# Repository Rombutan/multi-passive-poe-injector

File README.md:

# multi-passive-poe-injector

Has 4 polyfused in line passive poe injectors and 4 polyfused power outputs
All outputs selectable with jumper between off, straight input, and boost converter
All the outputs also have a fully analog status LED which indicated red for fuse blown, green for good, and blue for powered off via the jumper.
Uses wiedmullers and wagos for all wire connections

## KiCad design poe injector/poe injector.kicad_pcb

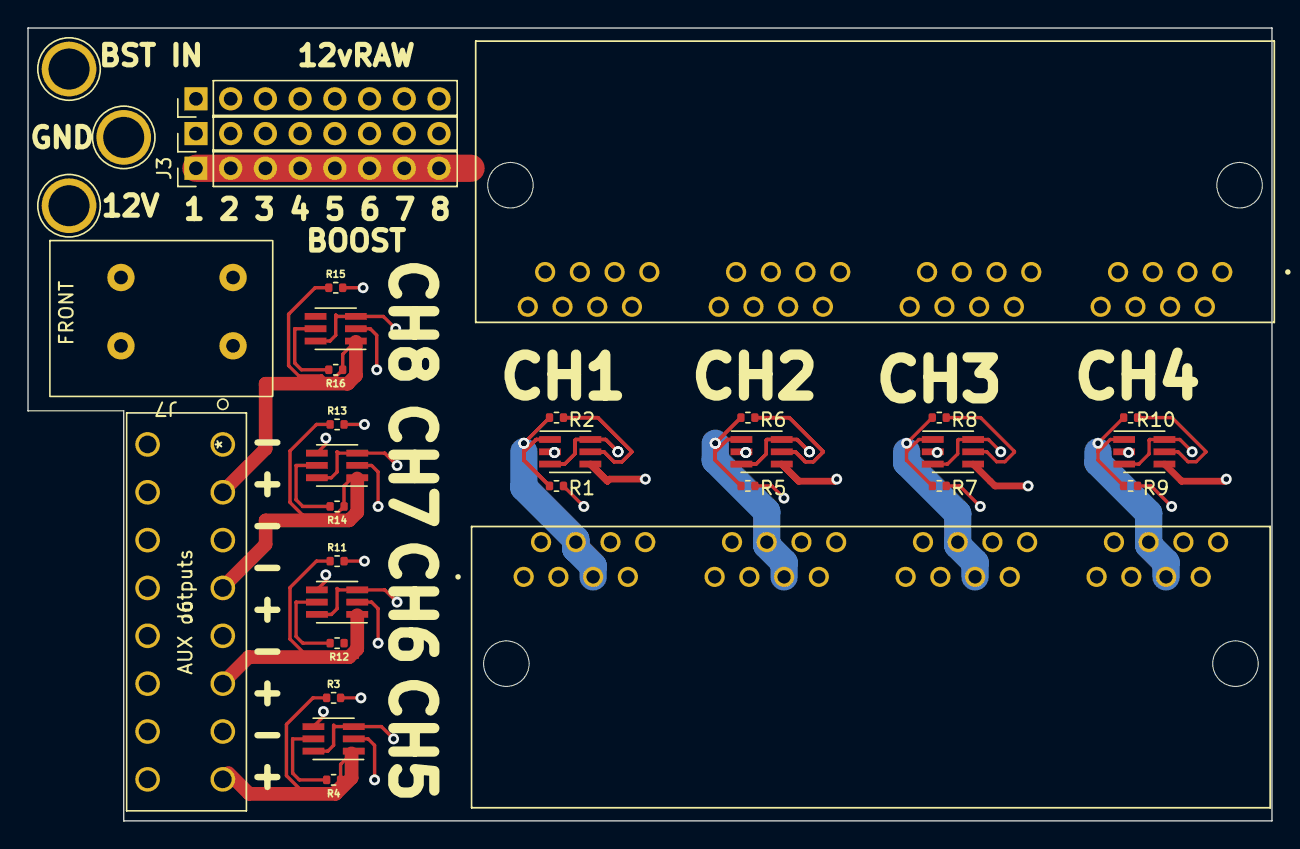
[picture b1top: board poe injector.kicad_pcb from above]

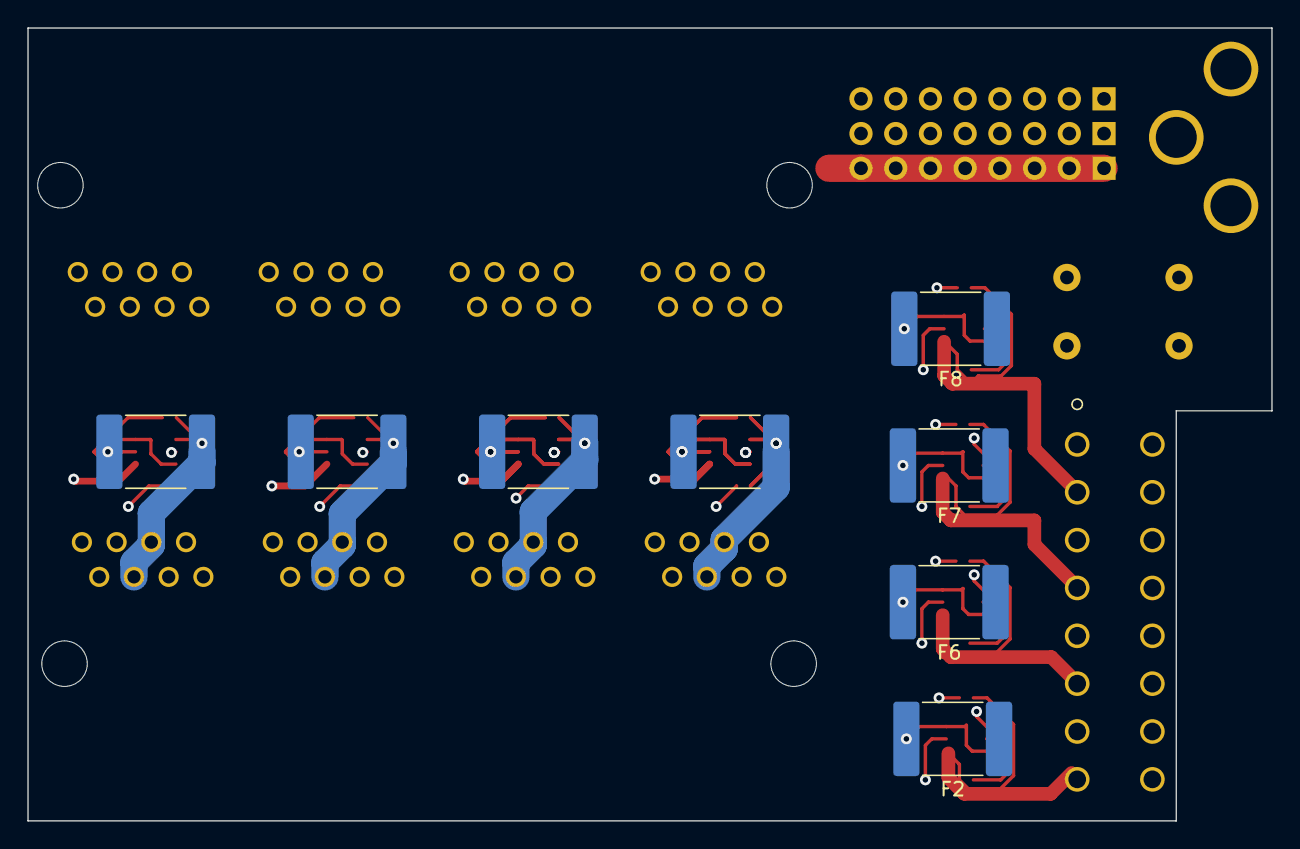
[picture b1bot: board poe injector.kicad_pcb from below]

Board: 4 copper layers, 91.0 x 58.0 mm, 42 parts (8 on the bottom side), 43 nets.

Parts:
D1, D2, D3, D4, D5, D6, D7, D8: LED_RGB; LED_Avago_PLCC6_3x2.8mm
F1, F2, F3, F4, F5, F6, F7, F8: Polyfuse; Fuse_2920_7451Metric
J1, J2: 5557562-1; TE_5557562-1
J3: BOOST; PinHeader_1x08_P2.54mm_Vertical
J4: MOD_IN; PinHeader_1x08_P2.54mm_Vertical
J5: 12v DIRECT; PinHeader_1x08_P2.54mm_Vertical
J6: AUX outputs; 1825700000
J7: Conn_01x02_Male; WAGO-2604-1102
R1, R2, R3, R4, R5, R6, R7, R8, R9, R10, R11, R12, R13, R14, R15, R16: 600; R_0402_1005Metric
TP1: 12v; TestPoint_Plated_Hole_D3.0mm
TP2: BOOST OUT; TestPoint_Plated_Hole_D3.0mm
TP3: GND; TestPoint_Plated_Hole_D3.0mm

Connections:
+12P: J3.1, J3.2, J3.3, J3.4, J3.5, J3.6, J3.7, J3.8, TP2.1
+12V: D1.4 (BA), D2.4 (BA), D3.4 (BA), D4.4 (BA), D5.4 (BA), D6.4 (BA), D7.4 (BA), D8.4 (BA), J5.1, J5.2, J5.3, J5.4, J5.5, J5.6, J5.7, J5.8, J7.1, TP1.1
/Aux Power1/PWR_OUT: D6.1 (RK), F6.1, J6.6, R11.1, R12.2
/Aux Power2/PWR_OUT: D7.1 (RK), F7.1, J6.4, R13.1, R14.2
/Aux Power3/PWR_OUT: D8.1 (RK), F8.1, J6.2, R15.1, R16.2
/Aux Power/PWR_OUT: D2.1 (RK), F2.1, J6.8, R3.1, R4.2
/Injector Block1/In1: J1.P2_1, J2.P3_1
/Injector Block1/In2: J1.P2_2, J2.P3_2
/Injector Block1/In3: J1.P2_3, J2.P3_3
/Injector Block1/In6: J1.P2_6, J2.P3_6
/Injector Block1/Out4: D3.1 (RK), F3.1, J1.P2_4, J1.P2_5, R5.1, R6.2
/Injector Block2/In1: J1.P3_1, J2.P2_1
/Injector Block2/In2: J1.P3_2, J2.P2_2
/Injector Block2/In3: J1.P3_3, J2.P2_3
/Injector Block2/In6: J1.P3_6, J2.P2_6
/Injector Block2/Out4: D4.1 (RK), F4.1, J1.P3_4, J1.P3_5, R7.1, R8.2
/Injector Block3/In1: J1.P4_1, J2.P1_1
/Injector Block3/In2: J1.P4_2, J2.P1_2
/Injector Block3/In3: J1.P4_3, J2.P1_3
/Injector Block3/In6: J1.P4_6, J2.P1_6
/Injector Block3/Out4: D5.1 (RK), F5.1, J1.P4_4, J1.P4_5, R9.1, R10.2
/Injector Block/In1: J1.P1_1, J2.P4_1
/Injector Block/In2: J1.P1_2, J2.P4_2
/Injector Block/In3: J1.P1_3, J2.P4_3
/Injector Block/In6: J1.P1_6, J2.P4_6
/Injector Block/Out4: D1.1 (RK), F1.1, J1.P1_4, J1.P1_5, R1.1, R2.2
AUX1_IN: D2.3 (BK), D2.6 (RA), F2.2, J4.5
AUX2_IN: D6.3 (BK), D6.6 (RA), F6.2, J4.6
AUX3_IN: D7.3 (BK), D7.6 (RA), F7.2, J4.7
AUX4_IN: D8.3 (BK), D8.6 (RA), F8.2, J4.8
GND: D1.2 (GK), D2.2 (GK), D3.2 (GK), D4.2 (GK), D5.2 (GK), D6.2 (GK), D7.2 (GK), D8.2 (GK), J1.P1_7, J1.P1_8, J1.P2_7, J1.P2_8, J1.P3_7, J1.P3_8, J1.P4_7, J1.P4_8, J6.1, J6.3, J6.5, J6.7, J7.2, R1.2, R3.2, R5.2, R7.2, R9.2, R11.2, R13.2, R15.2, TP3.1
unnamed: D1.5 (GA), R2.1
unnamed: D2.5 (GA), R4.1
unnamed: D3.5 (GA), R6.1
unnamed: D4.5 (GA), R8.1
unnamed: D5.5 (GA), R10.1
unnamed: D6.5 (GA), R12.1
unnamed: D7.5 (GA), R14.1
unnamed: D8.5 (GA), R16.1
POE1_PWR: D1.3 (BK), D1.6 (RA), F1.2, J4.1
POE2_PWR: D3.3 (BK), D3.6 (RA), F3.2, J4.2
POE3_PWR: D4.3 (BK), D4.6 (RA), F4.2, J4.3
POE4_PWR: D5.3 (BK), D5.6 (RA), F5.2, J4.4

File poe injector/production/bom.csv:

Designator,Footprint,Quantity,Value,LCSC Part #
"D1, D2, D3, D4, D5, D6, D7, D8",LED_Avago_PLCC6_3x2.8mm,8,LED_RGB,
"F1, F2, F3, F4, F5, F6, F7, F8",Fuse_2920_7451Metric,8,Polyfuse,
"J1, J2",TE_5557562-1,2,5557562-1,
J3,PinHeader_1x08_P2.54mm_Vertical,1,BOOST,
J4,PinHeader_1x08_P2.54mm_Vertical,1,MOD_IN,
J5,PinHeader_1x08_P2.54mm_Vertical,1,12v DIRECT,
J6,WAGO-2604-1108,1,AUX outputs,
J7,WAGO-2604-1102,1,PWR IN,
J8,WAGO-2604-1104,1,SMPS CONN,
"R1, R10, R11, R12, R13, R14, R15, R16, R2, R3, R4, R5, R6, R7, R8, R9",R_0402_1005Metric,16,600,

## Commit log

2022-12-28 add all the stuff from the past year
